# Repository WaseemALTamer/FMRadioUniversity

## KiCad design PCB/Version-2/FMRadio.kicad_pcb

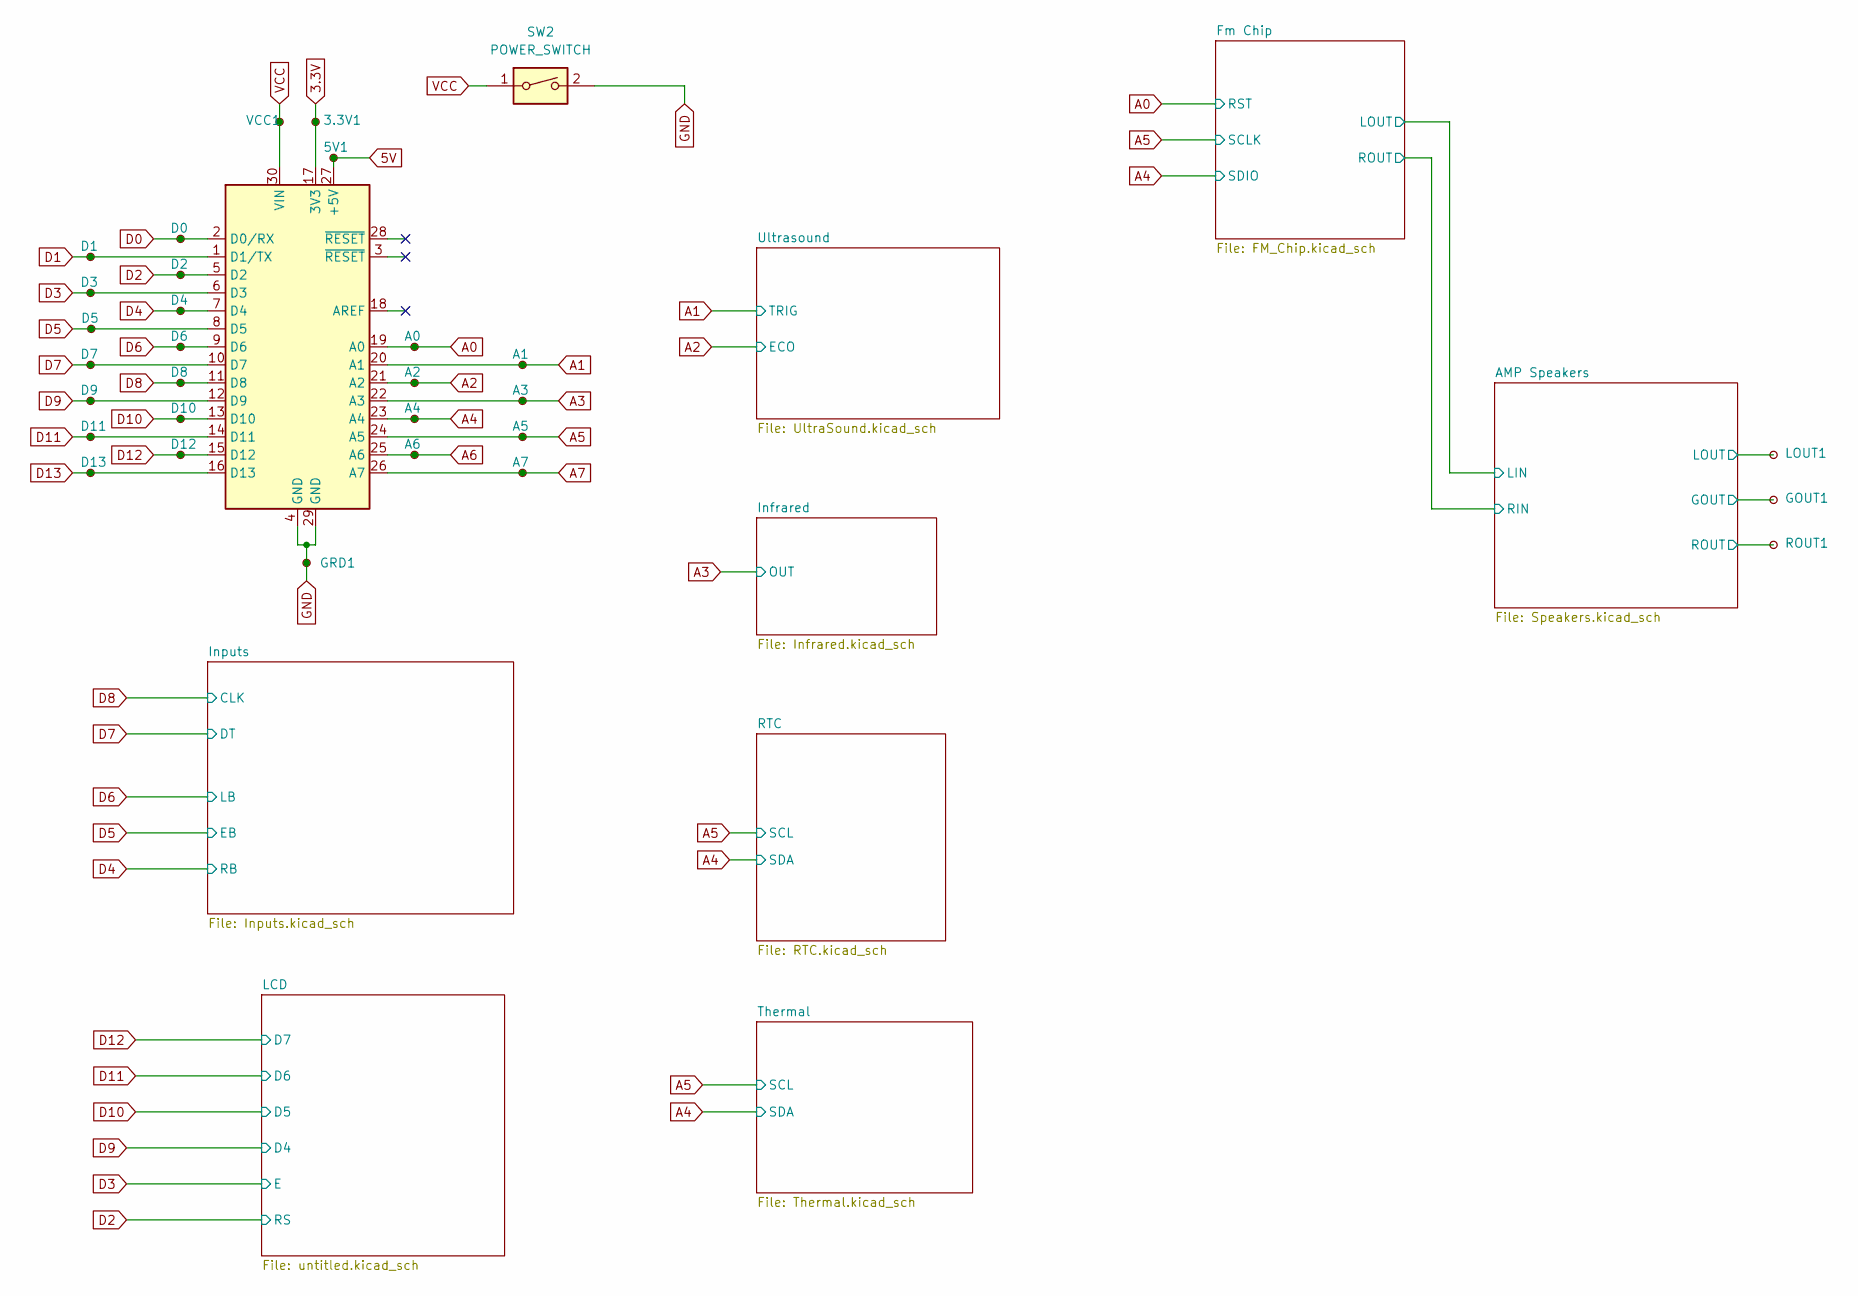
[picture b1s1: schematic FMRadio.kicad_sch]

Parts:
3.3V1, 5V1: TestPoint_Small; PinHeader_1x04_P2.54mm_Vertical_Custum_shortedpins
A0, A1, A2, A3, A4, A5, A6, A7: TestPoint_Small; PinHeader_1x04_P2.54mm_Vertical_Custum_shortedpins
AN1: Arduino_Nano_v3.x; Arduino_Nano
D0, D1, D2, D3, D4, D5, D6, D7, D8, D9, D10, D11, D12, D13: TestPoint_Small; PinHeader_1x04_P2.54mm_Vertical_Custum_shortedpins
GOUT1: PinHeader_1x04_P2.54mm_Vertical_Custum_shortedpins
GRD1: TestPoint_Small; PinHeader_1x04_P2.54mm_Vertical_Custum_shortedpins
LOUT1: PinHeader_1x04_P2.54mm_Vertical_Custum_shortedpins
ROUT1: PinHeader_1x04_P2.54mm_Vertical_Custum_shortedpins
SW2: POWER_SWITCH; PinHeader_1x02_P2.54mm_Vertical
VCC1: TestPoint_Small; PinHeader_1x04_P2.54mm_Vertical_Custum_shortedpins

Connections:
3.3V: 3.3V1.1, AN1.17 (3V3); also elsewhere on the board
5V: 5V1.1, AN1.27 (+5V); also elsewhere on the board
/AMP Speakers/LOUT: LOUT1.1; also elsewhere on the board
/AMP Speakers/ROUT: ROUT1.1; also elsewhere on the board
A0: A0.1, AN1.19 (A0); also elsewhere on the board
A1: A1.1, AN1.20 (A1); also elsewhere on the board
A2: A2.1, AN1.21 (A2); also elsewhere on the board
A3: A3.1, AN1.22 (A3); also elsewhere on the board
A4: A4.1, AN1.23 (A4); also elsewhere on the board
A5: A5.1, AN1.24 (A5); also elsewhere on the board
A6: A6.1, AN1.25 (A6)
A7: A7.1, AN1.26 (A7)
D0: AN1.2 (D0/RX), D0.1
D1: AN1.1 (D1/TX), D1.1
D2: AN1.5 (D2), D2.1; also elsewhere on the board
D3: AN1.6 (D3), D3.1; also elsewhere on the board
D4: AN1.7 (D4), D4.1; also elsewhere on the board
D5: AN1.8 (D5), D5.1; also elsewhere on the board
D6: AN1.9 (D6), D6.1; also elsewhere on the board
D7: AN1.10 (D7), D7.1; also elsewhere on the board
D8: AN1.11 (D8), D8.1; also elsewhere on the board
D9: AN1.12 (D9), D9.1; also elsewhere on the board
D10: AN1.13 (D10), D10.1; also elsewhere on the board
D11: AN1.14 (D11), D11.1; also elsewhere on the board
D12: AN1.15 (D12), D12.1; also elsewhere on the board
D13: AN1.16 (D13), D13.1
GND: AN1.4 (GND), AN1.29 (GND), GOUT1.1, GRD1.1, SW2.2; also elsewhere on the board
VCC: AN1.30 (VIN), SW2.1, VCC1.1; also elsewhere on the board

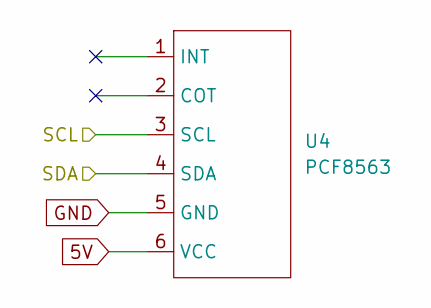
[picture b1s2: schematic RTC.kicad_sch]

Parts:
U4: PCF8563; PinHeader_1x06_P2.54mm_Vertical

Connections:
5V: U4.6 (VCC); also elsewhere on the board
A4: U4.4 (SDA); also elsewhere on the board
A5: U4.3 (SCL); also elsewhere on the board
GND: U4.5 (GND); also elsewhere on the board

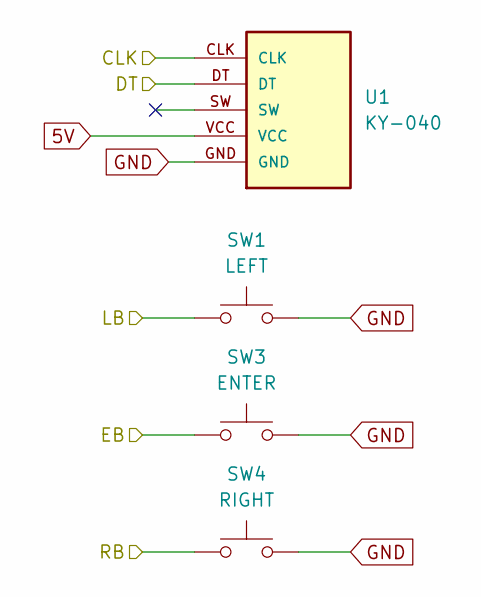
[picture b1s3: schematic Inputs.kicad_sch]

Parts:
SW1: LEFT; SW_PUSH_6mm_H4.3mm
SW3: ENTER; SW_PUSH_6mm_H4.3mm
SW4: RIGHT; SW_PUSH_6mm_H4.3mm
U1: KY-040; KY-040-PORT

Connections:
5V: U1.VCC; also elsewhere on the board
D4: SW4.1; also elsewhere on the board
D5: SW3.1; also elsewhere on the board
D6: SW1.1; also elsewhere on the board
D7: U1.DT; also elsewhere on the board
D8: U1.CLK; also elsewhere on the board
GND: SW1.2, SW3.2, SW4.2, U1.GND; also elsewhere on the board

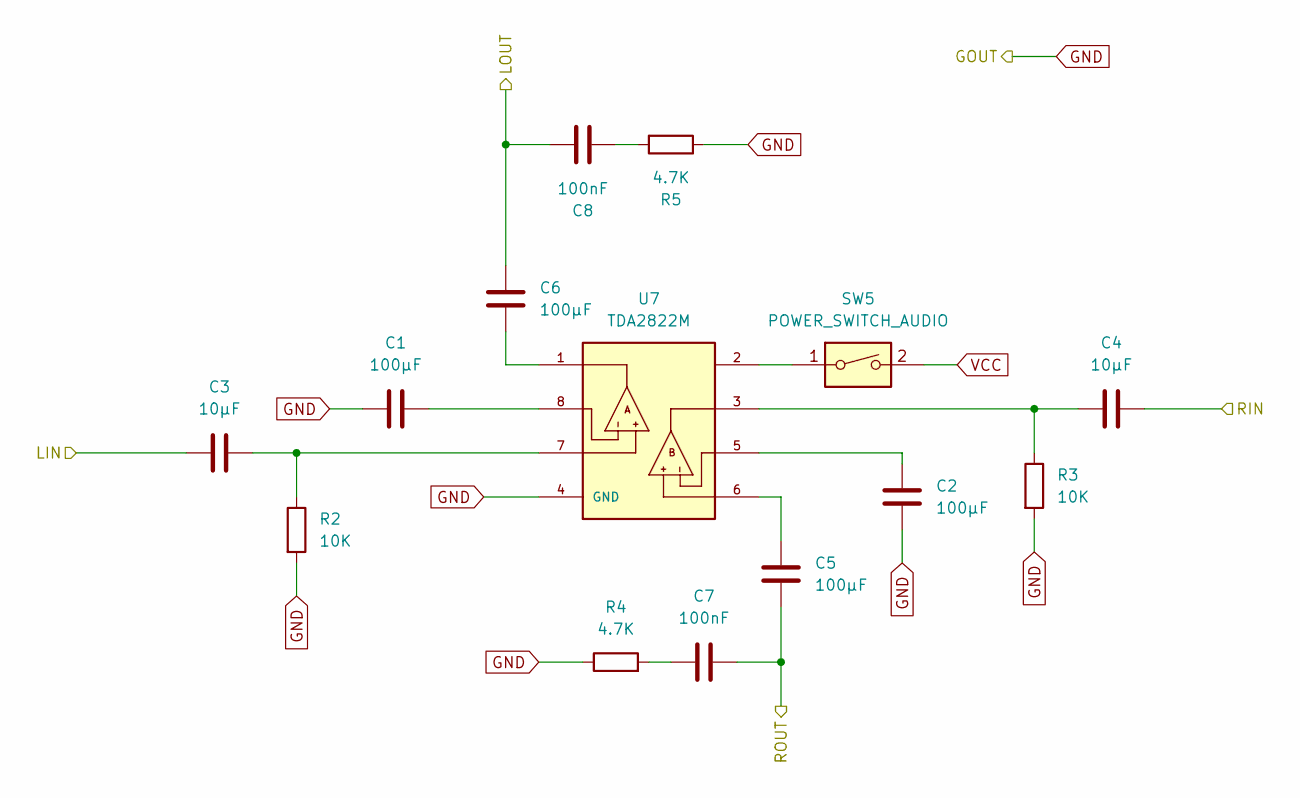
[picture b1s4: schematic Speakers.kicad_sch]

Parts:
C1, C2, C5, C6: 100μF; CP_Radial_D5.0mm_P2.50mm
C3, C4: 10μF; CP_Radial_D5.0mm_P2.50mm
C7, C8: 100nF; CP_Radial_D5.0mm_P2.50mm
R2, R3: 10K; R_Axial_DIN0207_L6.3mm_D2.5mm_P10.16mm_Horizontal
R4, R5: 4.7K; R_Axial_DIN0207_L6.3mm_D2.5mm_P10.16mm_Horizontal
SW5: POWER_SWITCH_AUDIO; PinHeader_1x02_P2.54mm_Vertical
U7: TDA2822M; DIP762W45P254L1092H508Q8; PARTREV September 2003

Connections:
/AMP Speakers/LIN: C3.1; also elsewhere on the board
/AMP Speakers/LOUT: C6.2, C8.1; also elsewhere on the board
/AMP Speakers/RIN: C4.2; also elsewhere on the board
/AMP Speakers/ROUT: C5.1, C7.1; also elsewhere on the board
GND: C1.1, C2.1, R2.2, R3.2, R4.1, R5.1, U7.4 (GND); also elsewhere on the board
unnamed: C1.2, U7.8
unnamed: C2.2, U7.5
unnamed: C3.2, R2.1, U7.7
unnamed: C4.1, R3.1, U7.3
unnamed: C5.2, U7.6
unnamed: C6.1, U7.1
unnamed: C7.2, R4.2
unnamed: C8.2, R5.2
unnamed: SW5.1, U7.2
VCC: SW5.2; also elsewhere on the board

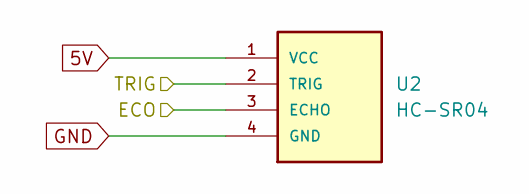
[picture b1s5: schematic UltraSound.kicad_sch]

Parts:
U2: HC-SR04; XCVR_HC-SR04

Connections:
5V: U2.1 (VCC); also elsewhere on the board
A1: U2.2 (TRIG); also elsewhere on the board
A2: U2.3 (ECHO); also elsewhere on the board
GND: U2.4 (GND); also elsewhere on the board

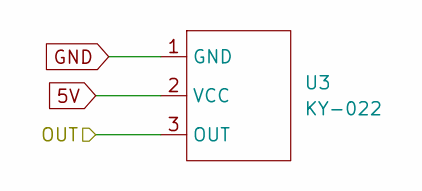
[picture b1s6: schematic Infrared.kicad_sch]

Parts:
U3: KY-022; PinHeader_1x03_P2.54mm_Vertical

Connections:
5V: U3.2 (VCC); also elsewhere on the board
A3: U3.3 (OUT); also elsewhere on the board
GND: U3.1 (GND); also elsewhere on the board

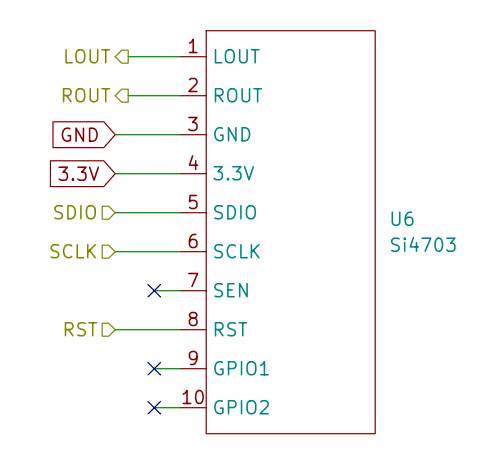
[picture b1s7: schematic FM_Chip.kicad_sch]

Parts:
U6: Si4703; PinHeader_1x10_P2.54mm_Vertical

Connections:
3.3V: U6.4 (3.3V); also elsewhere on the board
/AMP Speakers/LIN: U6.1 (LOUT); also elsewhere on the board
/AMP Speakers/RIN: U6.2 (ROUT); also elsewhere on the board
A0: U6.8 (RST); also elsewhere on the board
A4: U6.5 (SDIO); also elsewhere on the board
A5: U6.6 (SCLK); also elsewhere on the board
GND: U6.3 (GND); also elsewhere on the board

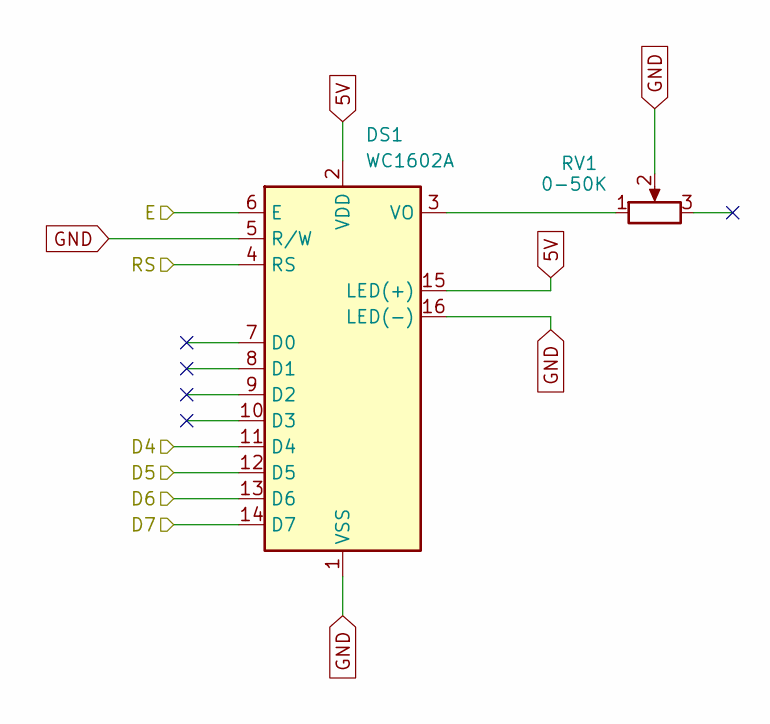
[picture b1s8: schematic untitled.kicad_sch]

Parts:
DS1: WC1602A
RV1: 0-50K; Potentiometer_Piher_PT-10-V10_Vertical

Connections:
5V: DS1.2 (VDD), DS1.15 (LED(+)); also elsewhere on the board
D2: DS1.4 (RS); also elsewhere on the board
D3: DS1.6 (E); also elsewhere on the board
D9: DS1.11 (D4); also elsewhere on the board
D10: DS1.12 (D5); also elsewhere on the board
D11: DS1.13 (D6); also elsewhere on the board
D12: DS1.14 (D7); also elsewhere on the board
GND: DS1.1 (VSS), DS1.5 (R/W), DS1.16 (LED(-)), RV1.2; also elsewhere on the board
unnamed: DS1.3 (VO), RV1.1

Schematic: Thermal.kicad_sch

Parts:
U5: HTU21D; PinHeader_1x04_P2.54mm_Vertical

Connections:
3.3V: U5.1 (3.3V); also elsewhere on the board
A4: U5.3 (SDA); also elsewhere on the board
A5: U5.4 (SCL); also elsewhere on the board
GND: U5.2 (GND); also elsewhere on the board

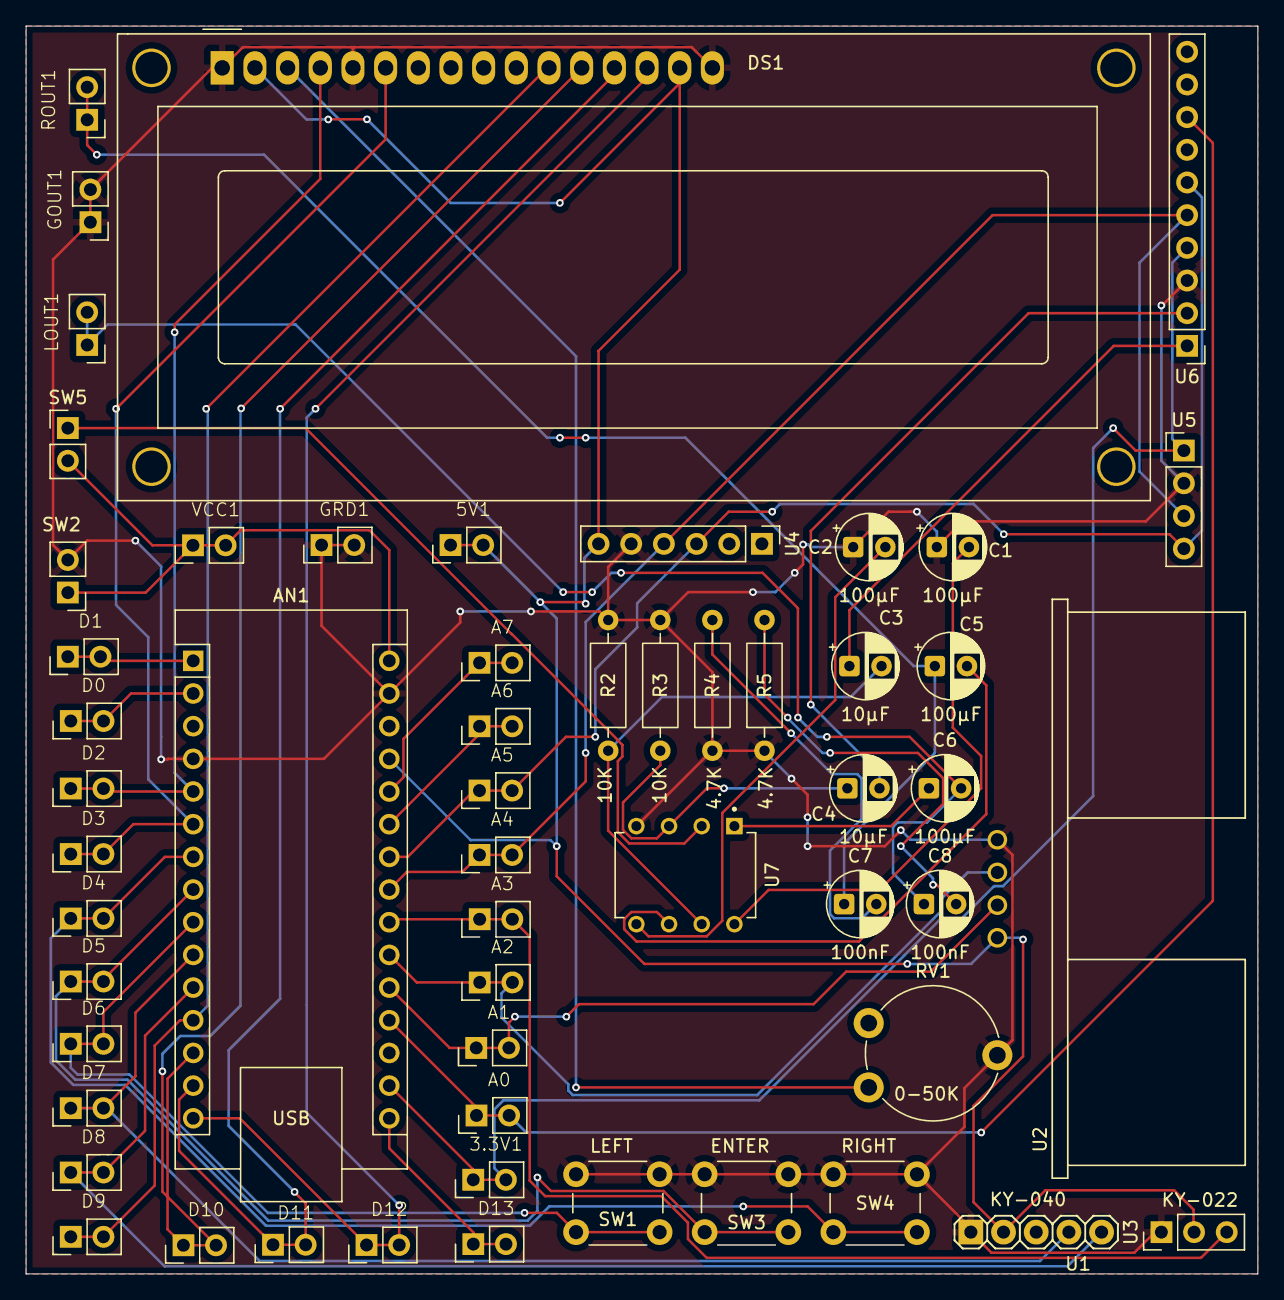
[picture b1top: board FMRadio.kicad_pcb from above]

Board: 2 copper layers, 95.8 x 97.0 mm, 56 parts (0 on the bottom side), 40 nets.

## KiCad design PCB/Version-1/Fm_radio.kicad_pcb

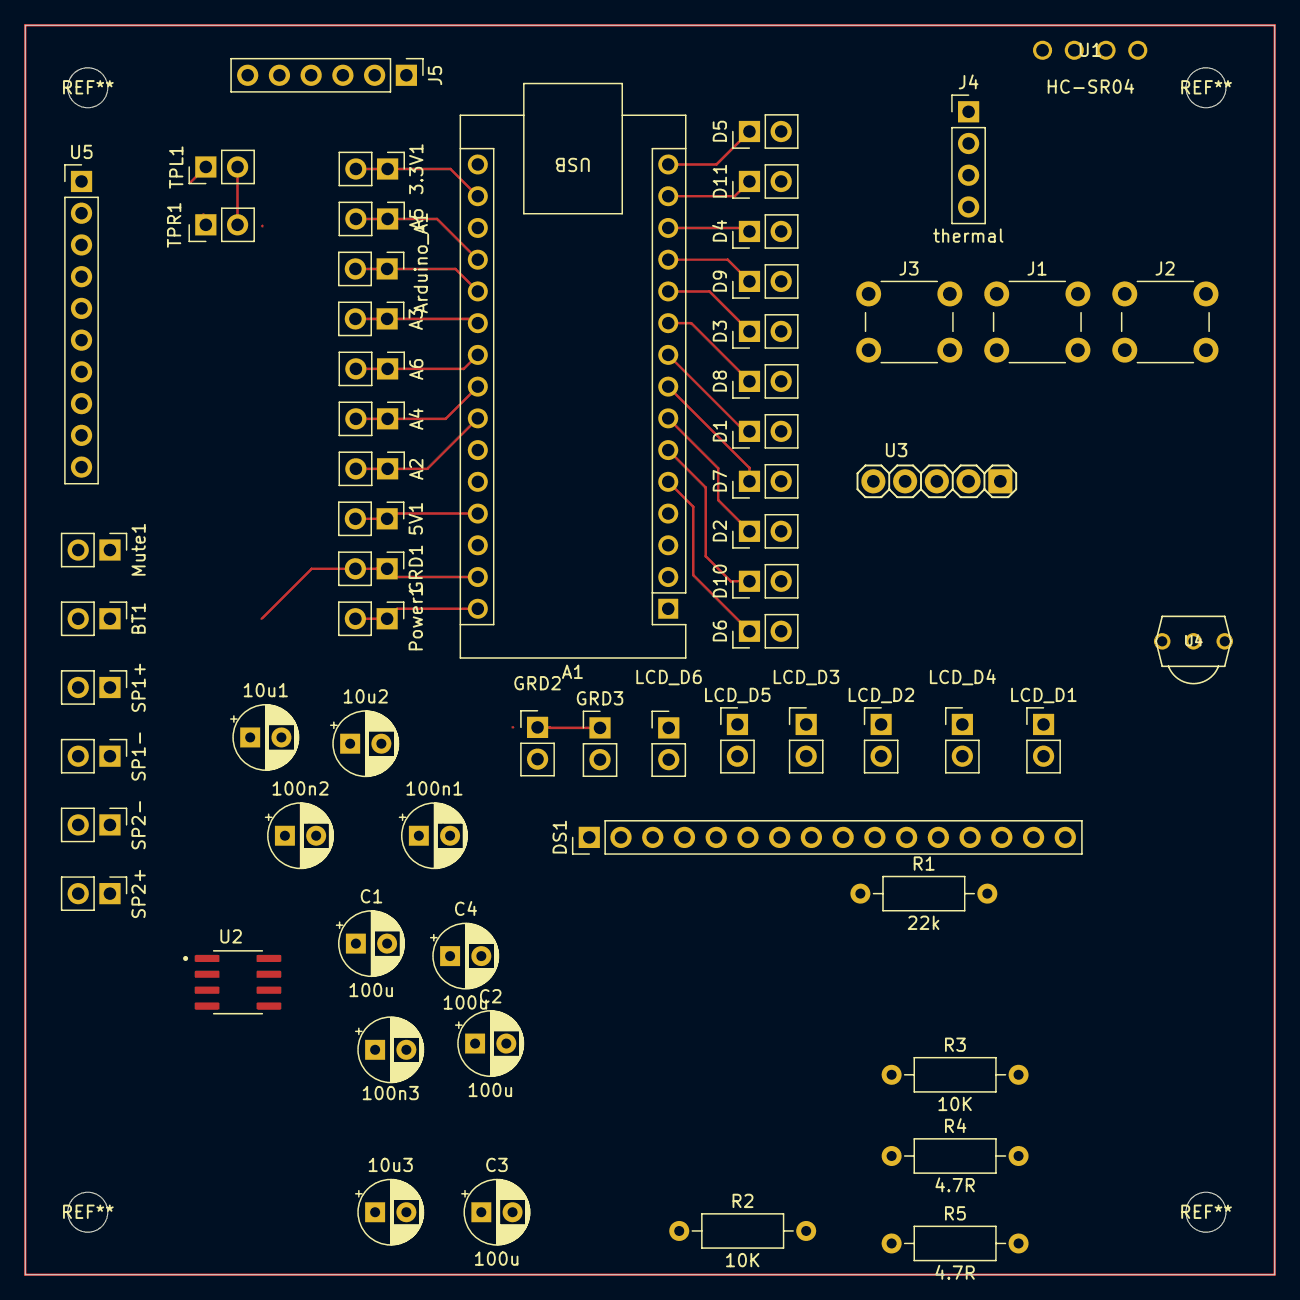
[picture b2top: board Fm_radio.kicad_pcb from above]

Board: 2 copper layers, 100.0 x 100.0 mm, 64 parts (0 on the bottom side), 36 nets.

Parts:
3.3V1: 3.3V; PinHeader_1x02_P2.54mm_Vertical
5V1: D2; PinHeader_1x02_P2.54mm_Vertical
10u1, 10u2, 10u3: C_Polarized; CP_Radial_D5.0mm_P2.50mm
100n1, 100n2, 100n3: C; CP_Radial_D5.0mm_P2.50mm
A1: Arduino_Nano_v3.x; Arduino_Nano
A2: A5; PinHeader_1x02_P2.54mm_Vertical
A3: A2; PinHeader_1x02_P2.54mm_Vertical
A4: A4; PinHeader_1x02_P2.54mm_Vertical
A5: A0; PinHeader_1x02_P2.54mm_Vertical
A6: A3; PinHeader_1x02_P2.54mm_Vertical
Arduino_A1: A1; PinHeader_1x02_P2.54mm_Vertical
BT1: Battery; PinHeader_1x02_P2.54mm_Vertical
C1, C2, C3, C4: 100u; CP_Radial_D5.0mm_P2.50mm
D1: D6; PinHeader_1x02_P2.54mm_Vertical
D2: D4; PinHeader_1x02_P2.54mm_Vertical
D3: D8; PinHeader_1x02_P2.54mm_Vertical
D4: D10; PinHeader_1x02_P2.54mm_Vertical
D5: D12; PinHeader_1x02_P2.54mm_Vertical
D6: D2; PinHeader_1x02_P2.54mm_Vertical
D7: D5; PinHeader_1x02_P2.54mm_Vertical
D8: D7; PinHeader_1x02_P2.54mm_Vertical
D9: D9; PinHeader_1x02_P2.54mm_Vertical
D10: D3; PinHeader_1x02_P2.54mm_Vertical
D11: D11; PinHeader_1x02_P2.54mm_Vertical
DS1: WC1602A; PinHeader_1x16_P2.54mm_Vertical
GRD1, GRD2, GRD3: GRD; PinHeader_1x02_P2.54mm_Vertical
J1: Button _enter; SW_PUSH_6mm
J2: Button _right; SW_PUSH_6mm
J3: Button _left; SW_PUSH_6mm
J4: thermal; PinHeader_1x04_P2.54mm_Vertical
J5: RTC; PinHeader_1x06_P2.54mm_Vertical
LCD_D1: D12; PinHeader_1x02_P2.54mm_Vertical
LCD_D2: D10; PinHeader_1x02_P2.54mm_Vertical
LCD_D3: D9; PinHeader_1x02_P2.54mm_Vertical
LCD_D4: D11; PinHeader_1x02_P2.54mm_Vertical
LCD_D5: D2; PinHeader_1x02_P2.54mm_Vertical
LCD_D6: D3; PinHeader_1x02_P2.54mm_Vertical
Mute1: TestPoint_2Pole; PinHeader_1x02_P2.54mm_Vertical
Power1: TestPoint_2Pole; PinHeader_1x02_P2.54mm_Vertical
R1: 22k; R_Axial_DIN0207_L6.3mm_D2.5mm_P10.16mm_Horizontal
R2, R3: 10K; R_Axial_DIN0207_L6.3mm_D2.5mm_P10.16mm_Horizontal
R4, R5: 4.7R; R_Axial_DIN0207_L6.3mm_D2.5mm_P10.16mm_Horizontal
SP1+, SP2+: +V OUT; PinHeader_1x02_P2.54mm_Vertical
SP1-, SP2-: -V OUT; PinHeader_1x02_P2.54mm_Vertical
TPL1: Left in; PinHeader_1x02_P2.54mm_Vertical
TPR1: Right in; PinHeader_1x02_P2.54mm_Vertical
U1: HC-SR04; XCVR_HC-SR04
U2: TDA2822D
U3: KY-040; KY-040-PORT
U4: TSOP1838; TSOP18XX
U5: PinHeader_1x10_P2.54mm_Vertical

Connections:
3.3V: 3.3V1.1, A1.17 (3V3), J4.1, U5.4 (VCC)
5V: 5V1.1, A1.27 (+5V), DS1.2 (VDD), DS1.15 (LED(+)), Mute1.1, U1.1 (VCC), U3.VCC, U4.VCC (V+)
/AMP Speakers/5V: 10u3.1, 100n1.1, Mute1.2, U2.2
/AMP Speakers/L_Speaker_in: 100n2.1, C3.2, SP1+.1
/AMP Speakers/L_out: 10u2.1, TPL1.1, U5.1 (L_out)
/AMP Speakers/R_Speaker_in: 100n3.1, C4.2, SP2+.1
/AMP Speakers/R_out: 10u1.1, TPR1.1, U5.2 (R_out)
A0: A1.19 (A0), A5.1, U5.8 (RST)
A1: A1.20 (A1), Arduino_A1.1, U1.2 (TRIG)
A2: A1.21 (A2), A3.1, U1.3 (ECHO)
A3: A1.22 (A3), A6.1, J5.6, U4.OUT
A4: A1.23 (A4), A4.1, J4.4, J5.3, U5.5 (SDIO)
A5: A1.24 (A5), A2.1, J4.3, J5.4, U5.6 (SCLK)
D2: A1.5 (D2), D6.1, DS1.6 (E), LCD_D5.1
D3: A1.6 (D3), D10.1, DS1.4 (RS), LCD_D6.1
D4: A1.7 (D4), D2.1, J1.2
D5: A1.8 (D5), D7.1, J2.2
D6: A1.9 (D6), D1.1, J3.2
D7: A1.10 (D7), D8.1, U3.DT
D8: A1.11 (D8), D3.1, U3.CLK
D9: A1.12 (D9), D9.1, DS1.11 (D4), LCD_D3.1
D10: A1.13 (D10), D4.1, DS1.12 (D5), LCD_D2.1
D11: A1.14 (D11), D11.1, DS1.13 (D6), LCD_D4.1
D12: A1.15 (D12), D5.1, DS1.14 (D7), LCD_D1.1
GRD: 10u3.2, 100n1.2, A1.4 (GND), A1.29 (GND), BT1.2 (-), C1.2, C2.2, DS1.1 (VSS), DS1.5 (R/W), DS1.16 (LED(-)), GRD1.1, GRD2.1, GRD3.1, J1.1, J2.1, J3.1, J4.2, J5.2, R1.2, R2.2, R3.2, R4.2, R5.2, SP1-.1, SP2-.1, U1.4 (GND), U2.4, U3.GND, U4.GND, U5.3 (GND)
unnamed: 10u1.2, R2.1, U2.7
unnamed: 10u2.2, R3.1, U2.6
unnamed: 100n2.2, R4.1
unnamed: 100n3.2, R5.1
unnamed: BT1.1 (+), Power1.2
unnamed: C1.1, U2.8
unnamed: C2.1, U2.5
unnamed: C3.1, U2.1
unnamed: C4.1, U2.3
unnamed: DS1.3 (VO), R1.1
VCC: A1.30 (VIN), Power1.1
